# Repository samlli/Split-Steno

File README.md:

# Split Stenographic Keyboard

**current working version: rev1.1**

Open source PCB design for a mirrored keyboard with the layout below:

**rev1.x Features:**

ATmega32u4 controller  
Mirrored Alps + MX compat  
3 x 1u / 2u + 1u bottom row layout support  
THT & SMD support  
<100x100mm square PCB size  
QMK firmware

**rev2.x Features:**

ATxmega controller  
nRF24L01+ wireless  
Per-key LED backlighting  
WS2812b underglow   
Wired & coin cell battery support  
Trackpoint support  
KeyPlus firmware

**rev3.x Features:**
Minimized PCB layout
Removed mirrored compat

## Build Guide

**required parts**

Quantities are for a single PCB, double required quantities if you build two halves!

- 1x Atxmega32a4u
- 17-18x MX / Alps switches
- 0-1x PCB mount stabilizer
- 1x PJ-320A TRRS jack
- 1x Hirose 5S8 USB Mini B
- 1x Fuse
- 4x 0.1uF Capacitors
- 1x 10uF Capacitor
- 2x 4.7k Resistor
- 1x Voltage Regulator (component name needed)

## Setup

Fancy K+ stuff goes here I guess

## Why?

**why is this keyboard a thing?**

Good question - I'm not quite sure to be honest... when you find out, let me know please

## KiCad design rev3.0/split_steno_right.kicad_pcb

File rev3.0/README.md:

# rev3.0

**Features:**

Minimized PCB footprint  
Lite version with core functionality only  
NRF and RGB moved to breakouts  
Routed GND with 0 vias

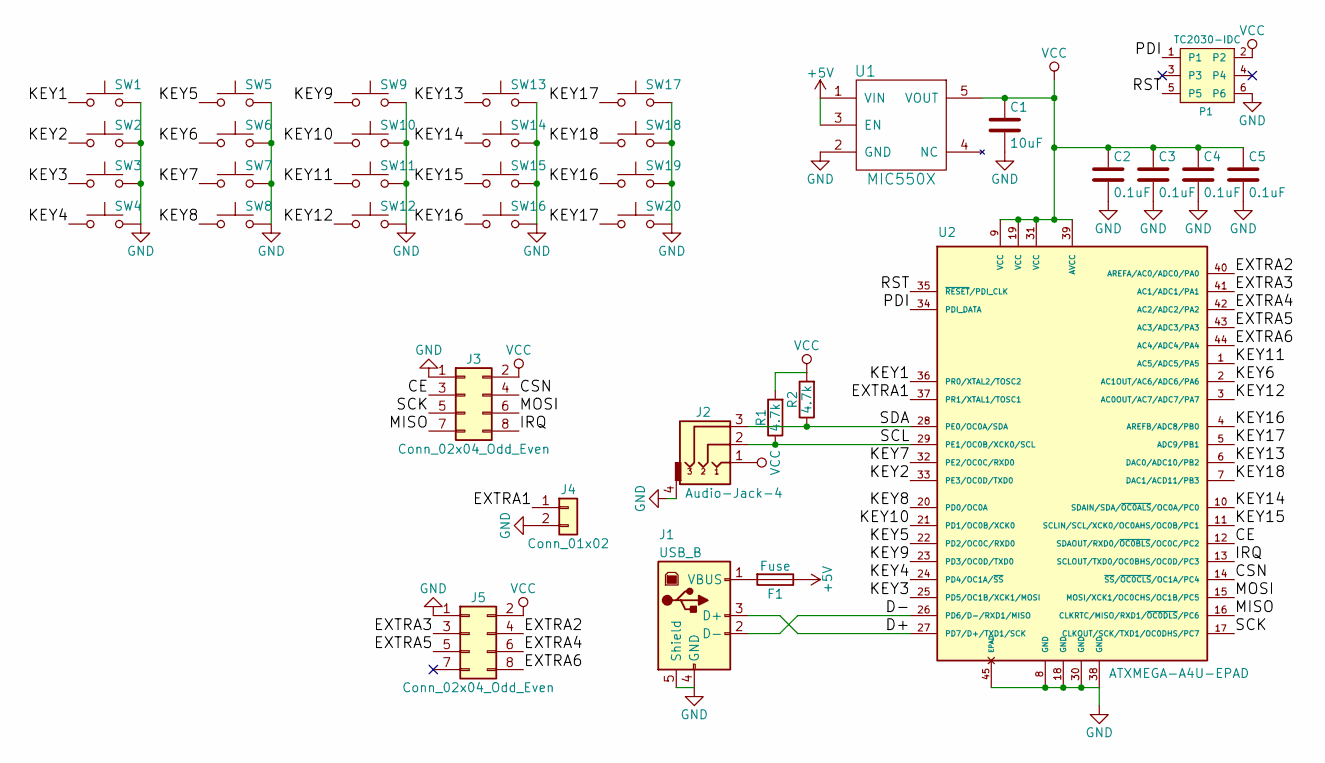
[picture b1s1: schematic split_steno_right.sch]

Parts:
C1: 10uF; C_0603_HandSoldering
C2, C3, C4, C5: 0.1uF; C_0603_HandSoldering
F1: Fuse; Fuse_SMD1206_HandSoldering
J1: USB_B; USB_miniB_hirose_5S8
J2: Audio-Jack-4; TRRS-PJ-320A
J3, J5: Conn_02x04_Odd_Even; Pin_Header_Straight_2x04_Pitch2.54mm
J4: Conn_01x02; Pin_Header_Straight_1x02_Pitch2.54mm
P1: TC2030-IDC; TC2030-NL_SMALL_AND_IDC_PDI
R1, R2: 4.7k; R_0603_HandSoldering
SW1, SW2, SW3, SW4, SW5, SW6, SW7, SW8, SW9, SW10, SW11, SW12, SW13, SW14, SW15, SW16, SW17, SW18: SW_Push; MX-1U-NoLED
SW19, SW20: SW_Push; MX-2U-NoLED
U1: MIC550X; SOT-23-5_HandSoldering
U2: ATXMEGA-A4U-EPAD; TQFP-44_10x10mm_Pitch0.8mm

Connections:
+5V: F1.1, U1.1 (VIN), U1.3 (EN)
/CE: J3.3, U2.12 (SDAOUT/RXD0/~OC0BLS~/OC0C/PC2)
/CSN: J3.4, U2.14 (~SS~/~OC0CLS~/OC1A/PC4)
/D+: J1.3 (D+), U2.27 (PD7/D+/TXD1/SCK)
/D-: J1.2 (D-), U2.26 (PD6/D-/RXD1/MISO)
/EXTRA1: J4.1, U2.37 (PR1/XTAL1/TOSC1)
/EXTRA2: J5.4, U2.40 (AREFA/AC0/ADC0/PA0)
/EXTRA3: J5.3, U2.41 (AC1/ADC1/PA1)
/EXTRA4: J5.6, U2.42 (AC2/ADC2/PA2)
/EXTRA5: J5.5, U2.43 (AC3/ADC3/PA3)
/EXTRA6: J5.8, U2.44 (AC4/ADC4/PA4)
/IRQ: J3.8, U2.13 (SCLOUT/TXD0/OC0BHS/OC0D/PC3)
/KEY1: SW1.1, U2.36 (PR0/XTAL2/TOSC2)
/KEY2: SW2.1, U2.33 (PE3/OC0D/TXD0)
/KEY3: SW3.1, U2.25 (PD5/OC1B/XCK1/MOSI)
/KEY4: SW4.1, U2.24 (PD4/OC1A/~SS~)
/KEY5: SW5.1, U2.22 (PD2/OC0C/RXD0)
/KEY6: SW6.1, U2.2 (AC1OUT/AC6/ADC6/PA6)
/KEY7: SW7.1, U2.32 (PE2/OC0C/RXD0)
/KEY8: SW8.1, U2.20 (PD0/OC0A)
/KEY9: SW9.1, U2.23 (PD3/OC0D/TXD0)
/KEY10: SW10.1, U2.21 (PD1/OC0B/XCK0)
/KEY11: SW11.1, U2.1 (AC5/ADC5/PA5)
/KEY12: SW12.1, U2.3 (AC0OUT/AC7/ADC7/PA7)
/KEY13: SW13.1, U2.6 (DAC0/ADC10/PB2)
/KEY14: SW14.1, U2.10 (SDAIN/SDA/~OC0ALS~/OC0A/PC0)
/KEY15: SW15.1, U2.11 (SCLIN/SCL/XCK0/OC0AHS/OC0B/PC1)
/KEY16: SW16.1, SW19.1, U2.4 (AREFB/ADC8/PB0)
/KEY17: SW17.1, SW20.1, U2.5 (ADC9/PB1)
/KEY18: SW18.1, U2.7 (DAC1/ACD11/PB3)
/MISO: J3.7, U2.16 (CLKRTC/MISO/RXD1/~OC0DLS~/PC6)
/MOSI: J3.6, U2.15 (MOSI/XCK1/OC0CHS/OC1B/PC5)
/PDI: P1.1, U2.34 (PDI_DATA)
/RST: P1.5, U2.35 (~RESET~/PDI_CLK)
/SCK: J3.5, U2.17 (CLKOUT/SCK/TXD1/OC0DHS/PC7)
/SCL: J2.2, R1.1, U2.29 (PE1/OC0B/XCK0/SCL)
/SDA: J2.3, R2.1, U2.28 (PE0/OC0A/SDA)
GND: C1.2, C2.2, C3.2, C4.2, C5.2, J1.4 (GND), J1.5 (Shield), J1.6, J2.4, J3.1, J4.2, J5.1, P1.6, SW1.2, SW2.2, SW3.2, SW4.2, SW5.2, SW6.2, SW7.2, SW8.2, SW9.2, SW10.2, SW11.2, SW12.2, SW13.2, SW14.2, SW15.2, SW16.2, SW17.2, SW18.2, SW19.2, SW20.2, U1.2 (GND), U2.8 (GND), U2.18 (GND), U2.30 (GND), U2.38 (GND), U2.45 (EPAD)
unnamed: F1.2, J1.1 (VBUS)
VCC: C1.1, C2.1, C3.1, C4.1, C5.1, J2.1, J3.2, J5.2, P1.2, R1.2, R2.2, U1.5 (VOUT), U2.9 (VCC), U2.19 (VCC), U2.31 (VCC), U2.39 (AVCC)

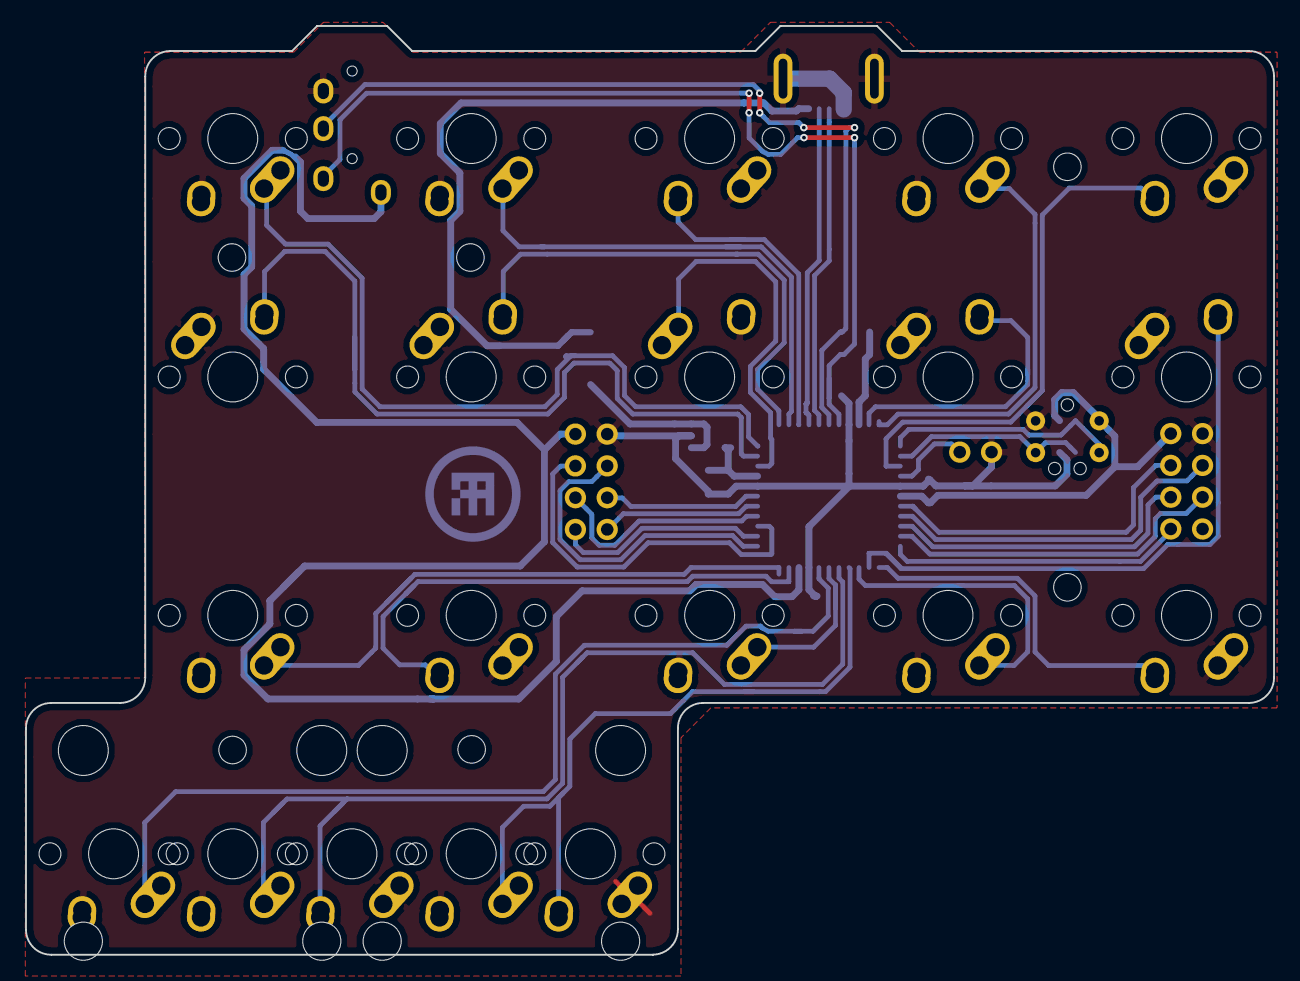
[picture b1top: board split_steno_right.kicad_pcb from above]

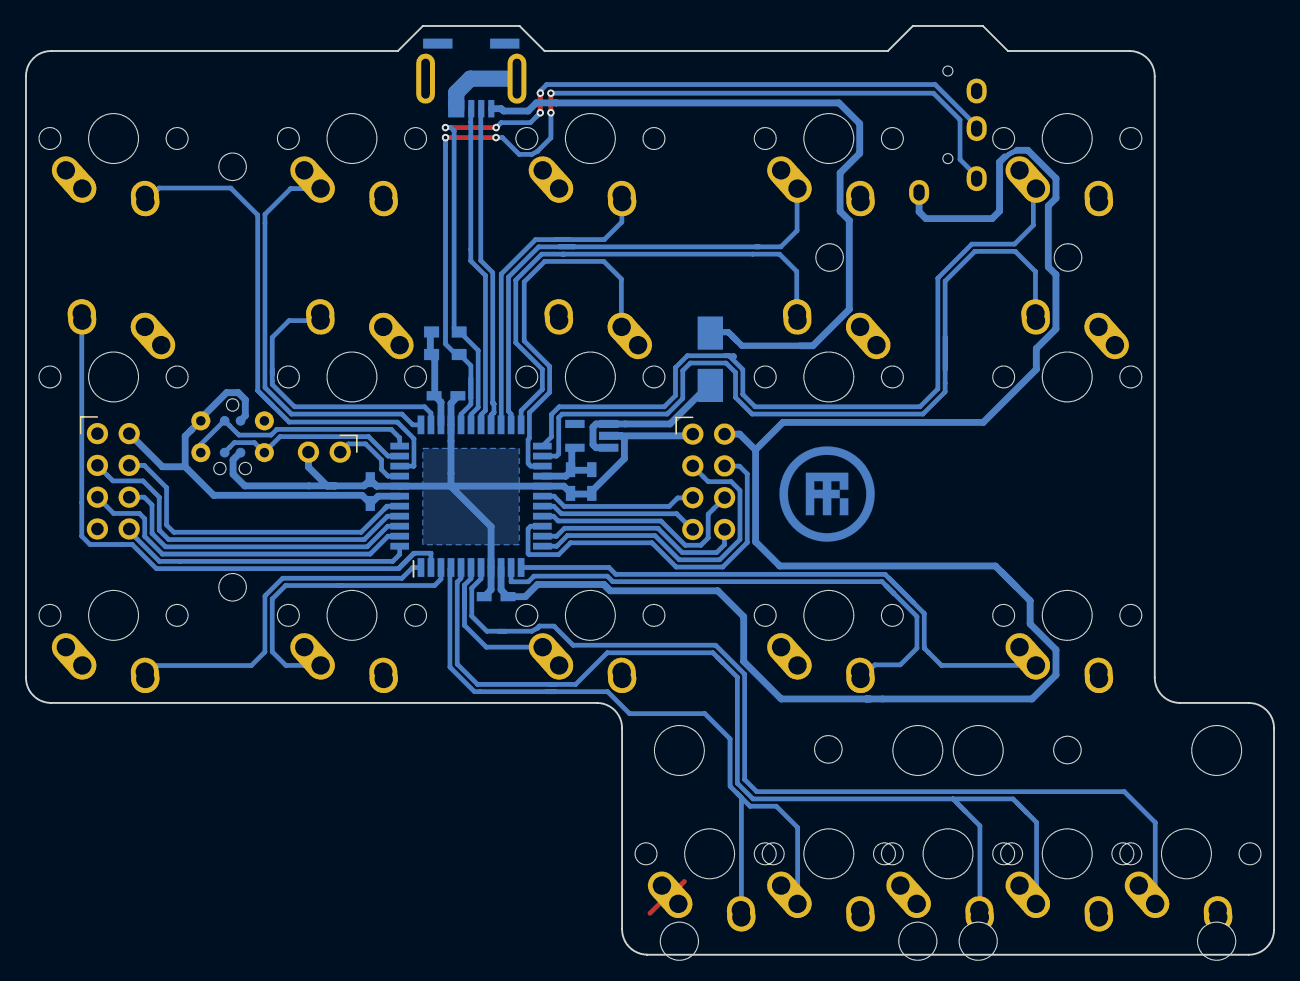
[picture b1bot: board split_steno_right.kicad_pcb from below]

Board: 2 copper layers, 99.7 x 74.2 mm, 42 parts (16 on the bottom side), 40 nets.

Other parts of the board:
M2, M2#2, M2#3, M2#4, M2#5, M2#6: MountingHole_2.2mm_M2

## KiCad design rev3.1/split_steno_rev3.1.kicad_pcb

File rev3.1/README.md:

# rev3.0

**Features:**

Integrated ATxmega controller  
SMD only  
No Diodes   
Wireless NRF

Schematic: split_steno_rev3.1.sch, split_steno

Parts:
BT1: Battery; CR2032_BK-913
C1, C2, C3, C4, C5, C6, C9, C10, C11, C12: 0.1uF; C_0603_HandSoldering
C8: 1uF; C_0603_HandSoldering
C13: 10uF; C_0603_HandSoldering
C14: 47uF; C_0603_HandSoldering
D1: D_Schottky_x2_KCom_AAK; SOT-23_Handsoldering
F1: Fuse; Fuse_SMD1206_HandSoldering
J1: USB_OTG; USB_miniB_hirose_5S8
J2: Audio-Jack-4; TRRS-PJ-320A
J3: Conn_01x03; Pin_Header_Straight_1x03_Pitch2.54mm
JP1: BAT CHK; Jumper_1x02_P2.54mm_THT
JP2: NO SW; Jumper_1x02_P2.54mm_THT
LED1, LED2, LED3, LED4, LED5, LED6: WS2812B
P1: TC2030-IDC; TC2030-NL_SMALL_AND_IDC_PDI
R4, R5: 100k; R_0603_HandSoldering
R6: 10k; R_0603_HandSoldering
R7, R8: 4.7k; R_0603_HandSoldering
SW1, SW2, SW3, SW4, SW5, SW6, SW7, SW8, SW9, SW10, SW11, SW12, SW13, SW14, SW15, SW16, SW17, SW18: SW_Push; MX-1U-NoLED
SW19, SW20: SW_Push; MX-2U-NoLED
SW21: SW_Push; SW_Tactile_SPST_Angled_MJTP1117
SW22: Switch-6P-2S2T; SlideSwitch_C&K_JS202011CQN
U1: 74LVC1G34; SOT-353_SC-70-5_Handsoldering
U4: MCP1700; SOT-23_Handsoldering
U5: ATXMEGA128A4U-AU; TQFP-44_10x10mm_Pitch0.8mm
U6: nRF24L01_module; NRF24L01-Module-SMD

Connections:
+3V3: J2.1, R7.1, R8.1
+5V: C1.1, C2.1, C3.1, C4.1, C5.1, C6.1, F1.2, LED1.1 (VDD), LED2.1 (VDD), LED3.1 (VDD), LED4.1 (VDD), LED5.1 (VDD), LED6.1 (VDD), R4.1, U1.5 (VCC), U4.3 (VI)
+BATT: D1.2, JP2.2, SW22.1, SW22.4
/BAT_LVL: JP1.2, U5.32 (PE2/OC0C/RXD0)
/CE: U5.13 (SCLOUT/TXD0/OC0BHS/OC0D/PC3), U6.3 (CE)
/CSN: U5.14 (~SS~/~OC0CLS~/OC1A/PC4), U6.4 (CSN)
/D+: J1.3 (D+), U5.27 (PD7/D+/TXD1/SCK/CLKOUT/EVOUT)
/D-: J1.2 (D-), U5.26 (PD6/D-/RXD1/MISO)
/IRQ: U5.12 (SDAOUT/RXD0/~OC0BLS~/OC0C/PC2), U6.8 (IRQ)
/KEY1: SW1.1, U5.25 (PD5/OC1B/XCK1/MOSI)
/KEY2: SW2.1, U5.24 (PD4/OC1A/~SS~)
/KEY3: SW3.1, U5.5 (ADC9/PB1)
/KEY4: SW4.1, U5.4 (AREFB/ADC8/PB0)
/KEY5: SW5.1, U5.3 (AC0OUT/AC7/ADC7/PA7)
/KEY6: SW6.1, U5.22 (PD2/OC0C/RXD0)
/KEY7: SW7.1, U5.23 (PD3/OC0D/TXD0)
/KEY8: SW8.1, U5.41 (AC1/ADC1/PA1)
/KEY9: SW9.1, U5.1 (AC5/ADC5/PA5)
/KEY10: SW10.1, U5.2 (AC1OUT/AC6/ADC6/PA6)
/KEY11: SW11.1, U5.21 (PD1/OC0B/XCK0)
/KEY12: SW12.1, U5.20 (PD0/OC0A)
/KEY13: SW13.1, U5.40 (AREFA/AC0/ADC0/PA0)
/KEY14: SW14.1, U5.37 (PR1/XTAL1/TOSC1)
/KEY15: SW15.1, U5.36 (PR0/XTAL2/TOSC2)
/KEY16: SW16.1, U5.42 (AC2/ADC2/PA2)
/KEY17: SW17.1, SW19.1, U5.43 (AC3/ADC3/PA3)
/KEY18: SW18.1, SW20.1, U5.44 (AC4/ADC4/PA4)
/MISO: U5.16 (CLKRTC/MISO/RXD1/~OC0DLS~/PC6), U6.7 (MISO)
/MOSI: U5.15 (MOSI/XCK1/OC0CHS/OC1B/PC5), U6.6 (MOSI)
/PDI: P1.1, U5.34 (PDI_DATA)
/RST: P1.5, R6.2, SW21.2, U5.35 (~RESET~/PDI_CLK)
/SCK: U5.17 (EVOUT/CLKOUT/SCK/TXD1/OC0DHS/PC7), U6.5 (SCK)
/SCL: J2.2, R8.2, U5.29 (PE1/OC0B/XCK0/SCL)
/SDA: J2.3, R7.2, U5.28 (PE0/OC0A/SDA)
/UNDER_LED: U1.2, U5.11 (SCLIN/SCL/XCK0/OC0AHS/OC0B/PC1)
/VBUS_CHECK: R4.2, R5.1, U5.33 (PE3/OC0D/TXD0)
GND: BT1.2, C1.2, C2.2, C3.2, C4.2, C5.2, C6.2, C8.2, C9.2, C10.2, C11.2, C12.2, C13.2, C14.2, J1.5 (GND), J2.4, LED1.3 (VSS), LED2.3 (VSS), LED3.3 (VSS), LED4.3 (VSS), LED5.3 (VSS), LED6.3 (VSS), P1.6, R5.2, SW1.2, SW2.2, SW3.2, SW4.2, SW5.2, SW6.2, SW7.2, SW8.2, SW9.2, SW10.2, SW11.2, SW12.2, SW13.2, SW14.2, SW15.2, SW16.2, SW17.2, SW18.2, SW19.2, SW20.2, SW21.1, U1.3 (GND), U4.1 (GND), U5.8 (GND), U5.18 (GND), U5.30 (GND), U5.38 (GND), U6.2 (VSS)
unnamed: BT1.1, JP1.1, JP2.1, SW22.2, SW22.5
unnamed: C8.1, D1.1, U4.2 (VO)
unnamed: F1.1, J1.1 (VBUS)
unnamed: J3.1, U5.6 (DAC0/ADC10/PB2)
unnamed: J3.2, U5.7 (DAC1/ACD11/PB3)
unnamed: J3.3, U5.10 (SDAIN/SDA/~OC0ALS~/OC0A/PC0)
unnamed: LED1.2 (DOUT), LED2.4 (DIN)
unnamed: LED1.4 (DIN), U1.4
unnamed: LED2.2 (DOUT), LED3.4 (DIN)
unnamed: LED3.2 (DOUT), LED4.4 (DIN)
unnamed: LED4.2 (DOUT), LED5.4 (DIN)
unnamed: LED5.2 (DOUT), LED6.4 (DIN)
VCC: C9.1, C10.1, C11.1, C12.1, C13.1, C14.1, D1.3, P1.2, R6.1, U5.9 (VCC), U5.19 (VCC), U5.31 (VCC), U5.39 (AVCC), U6.1 (VDD)

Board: 2 copper layers, 65 parts (39 on the bottom side), 50 nets, no tracks yet.

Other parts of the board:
M2, M2#2, M2#3, M2#4, M2#5, M2#6: MountingHole_2.2mm_M2

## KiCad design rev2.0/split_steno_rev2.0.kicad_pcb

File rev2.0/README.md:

# rev2.0

**WARNING: INCOMPLETE/ABANDONED**

Reason: big forehead, decided to scrap and proceed with 2.1

**Features:**

Integrated ATxmega controller  
SMD only  
No Diodes  
Reversible PCB

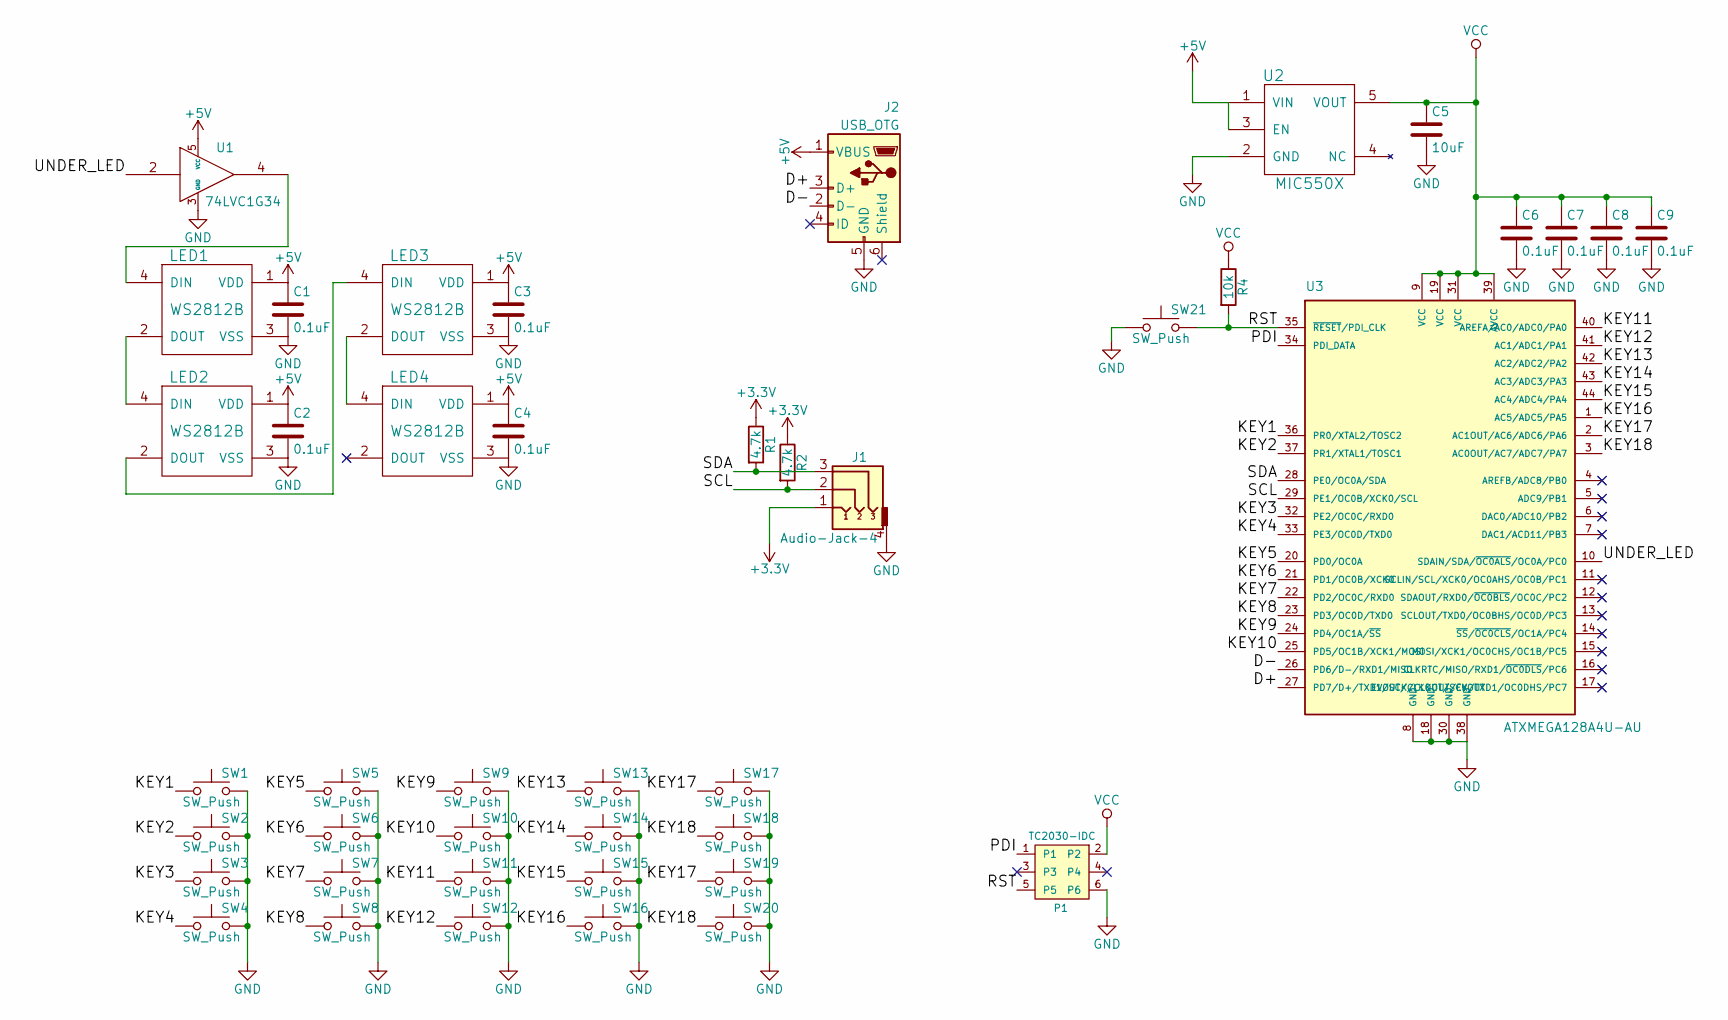
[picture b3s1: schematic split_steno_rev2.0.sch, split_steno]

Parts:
C1, C2, C3, C4, C6, C7, C8, C9: 0.1uF; C_0603_HandSoldering
C5: 10uF; C_0603_HandSoldering
J1: Audio-Jack-4; TRRS-PJ-320A
J2: USB_OTG; USB_miniB
LED1, LED2, LED3, LED4: WS2812B
P1: TC2030-IDC; Tag-Connect_TC2030-IDC-NL
R1, R2: 4.7k; R_0603_HandSoldering
R4: 10k; R_0603_HandSoldering
SW1, SW2, SW3, SW4, SW5, SW6, SW7, SW8, SW9, SW10, SW11, SW12, SW13, SW14, SW15, SW16, SW17, SW18: SW_Push; Hybrid_PCB_100H_Dual_hole
SW19, SW20: SW_Push; Hybrid_PCB_200H-dual-nosilk
SW21: SW_Push; SwitchPush_C&K_MultiFoot_RS-187R05A2-DS_And_PTS645_SMT
U1: 74LVC1G34; SOT-353_SC-70-5_Handsoldering
U2: MIC550X; SOT-23-5_HandSoldering
U3: ATXMEGA128A4U-AU; TQFP-44_10x10mm_Pitch0.8mm

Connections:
+3V3: J1.1, R1.1, R2.1
+5V: C1.1, C2.1, C3.1, C4.1, J2.1 (VBUS), LED1.1 (VDD), LED2.1 (VDD), LED3.1 (VDD), LED4.1 (VDD), U1.5 (VCC), U2.1 (VIN), U2.3 (EN)
/D+: J2.3 (D+), U3.27 (PD7/D+/TXD1/SCK/CLKOUT/EVOUT)
/D-: J2.2 (D-), U3.26 (PD6/D-/RXD1/MISO)
/KEY1: SW1.1, U3.36 (PR0/XTAL2/TOSC2)
/KEY2: SW2.1, U3.37 (PR1/XTAL1/TOSC1)
/KEY3: SW3.1, U3.32 (PE2/OC0C/RXD0)
/KEY4: SW4.1, U3.33 (PE3/OC0D/TXD0)
/KEY5: SW5.1, U3.20 (PD0/OC0A)
/KEY6: SW6.1, U3.21 (PD1/OC0B/XCK0)
/KEY7: SW7.1, U3.22 (PD2/OC0C/RXD0)
/KEY8: SW8.1, U3.23 (PD3/OC0D/TXD0)
/KEY9: SW9.1, U3.24 (PD4/OC1A/~SS~)
/KEY10: SW10.1, U3.25 (PD5/OC1B/XCK1/MOSI)
/KEY11: SW11.1, U3.40 (AREFA/AC0/ADC0/PA0)
/KEY12: SW12.1, U3.41 (AC1/ADC1/PA1)
/KEY13: SW13.1, U3.42 (AC2/ADC2/PA2)
/KEY14: SW14.1, U3.43 (AC3/ADC3/PA3)
/KEY15: SW15.1, U3.44 (AC4/ADC4/PA4)
/KEY16: SW16.1, U3.1 (AC5/ADC5/PA5)
/KEY17: SW17.1, SW19.1, U3.2 (AC1OUT/AC6/ADC6/PA6)
/KEY18: SW18.1, SW20.1, U3.3 (AC0OUT/AC7/ADC7/PA7)
/PDI: P1.1, U3.34 (PDI_DATA)
/RST: P1.5, R4.2, SW21.2, U3.35 (~RESET~/PDI_CLK)
/SCL: J1.2, R2.2, U3.29 (PE1/OC0B/XCK0/SCL)
/SDA: J1.3, R1.2, U3.28 (PE0/OC0A/SDA)
/UNDER_LED: U1.2, U3.10 (SDAIN/SDA/~OC0ALS~/OC0A/PC0)
GND: C1.2, C2.2, C3.2, C4.2, C5.2, C6.2, C7.2, C8.2, C9.2, J1.4, J2.5 (GND), LED1.3 (VSS), LED2.3 (VSS), LED3.3 (VSS), LED4.3 (VSS), P1.6, SW1.2, SW2.2, SW3.2, SW4.2, SW5.2, SW6.2, SW7.2, SW8.2, SW9.2, SW10.2, SW11.2, SW12.2, SW13.2, SW14.2, SW15.2, SW16.2, SW17.2, SW18.2, SW19.2, SW20.2, SW21.1, U1.3 (GND), U2.2 (GND), U3.8 (GND), U3.18 (GND), U3.30 (GND), U3.38 (GND)
unnamed: LED1.2 (DOUT), LED2.4 (DIN)
unnamed: LED1.4 (DIN), U1.4
unnamed: LED2.2 (DOUT), LED3.4 (DIN)
unnamed: LED3.2 (DOUT), LED4.4 (DIN)
VCC: C5.1, C6.1, C7.1, C8.1, C9.1, P1.2, R4.1, U2.5 (VOUT), U3.9 (VCC), U3.19 (VCC), U3.31 (VCC), U3.39 (AVCC)

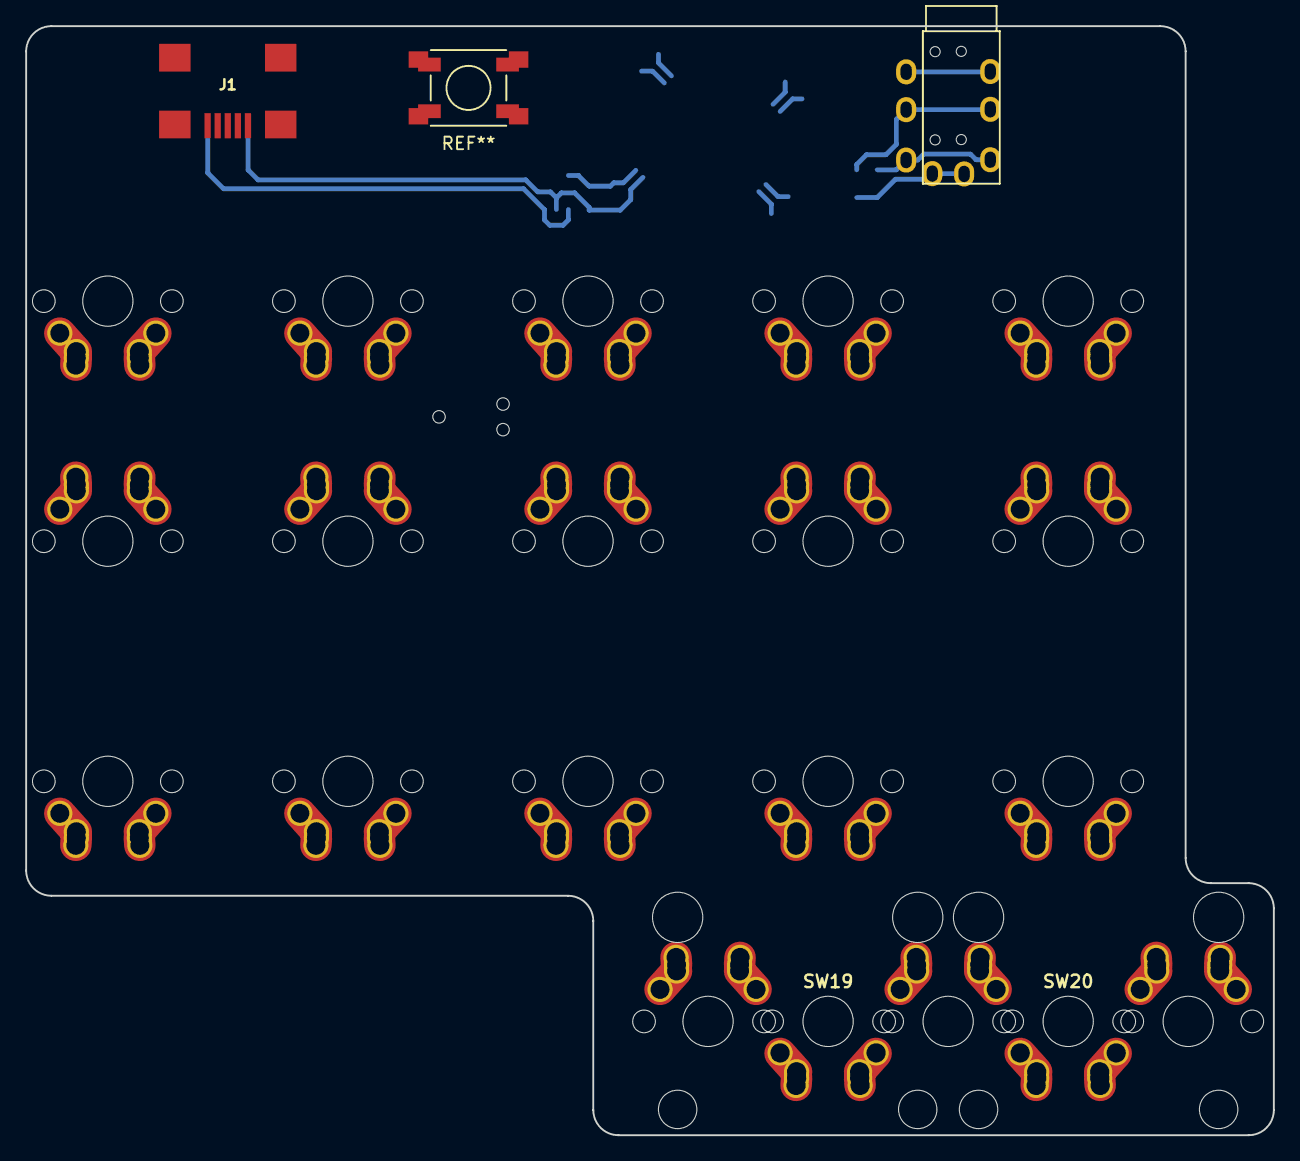
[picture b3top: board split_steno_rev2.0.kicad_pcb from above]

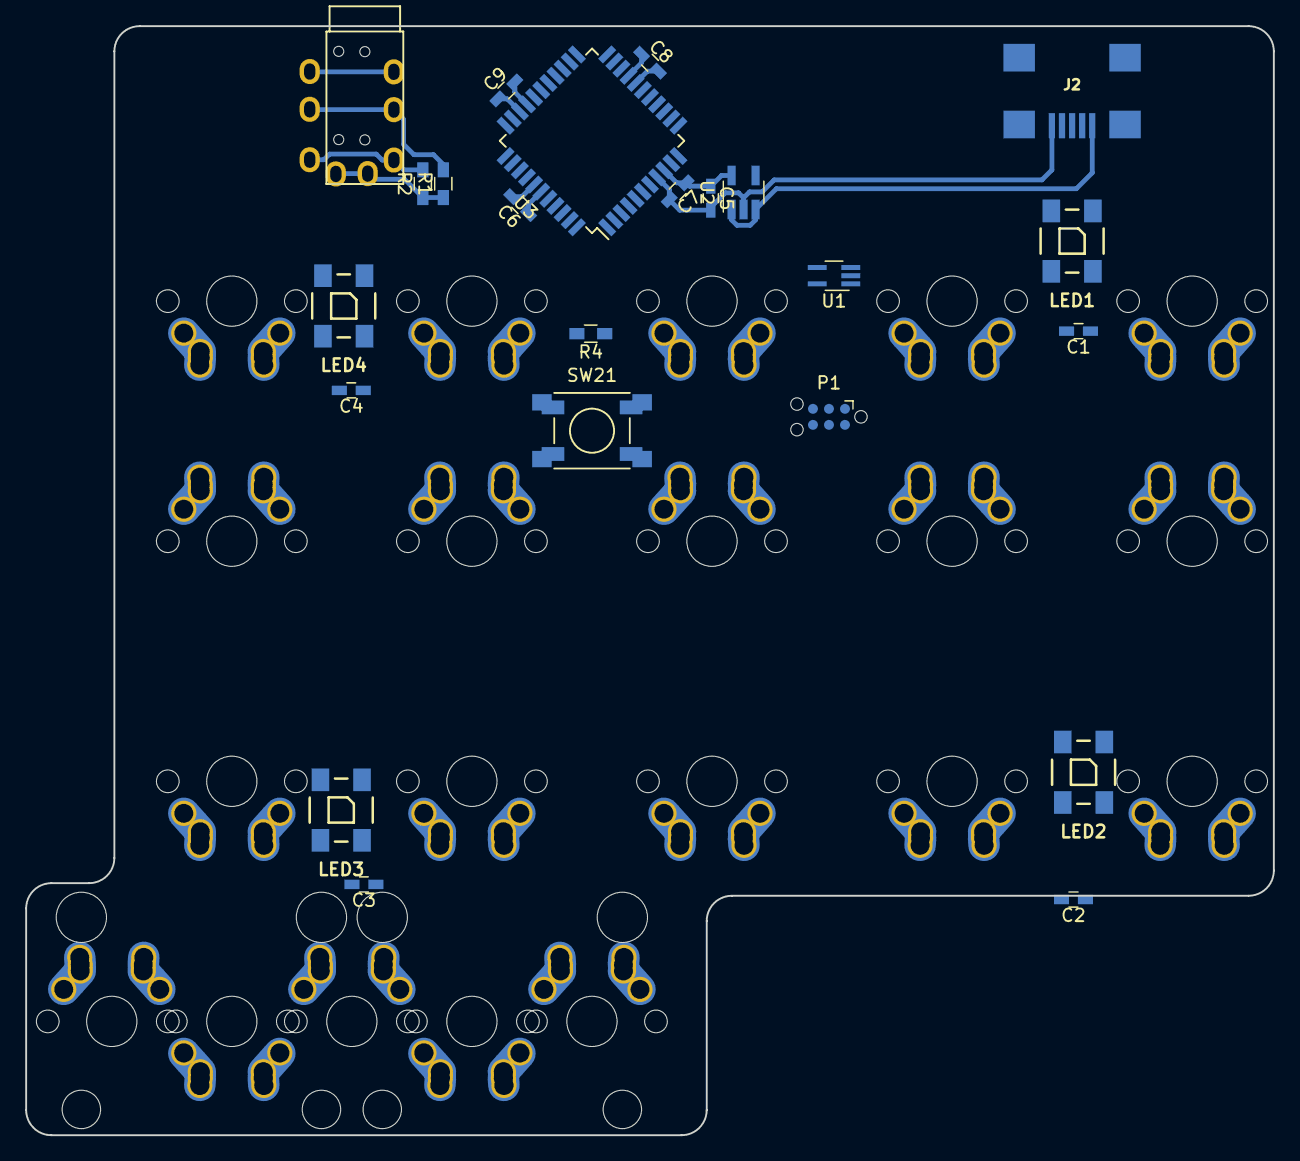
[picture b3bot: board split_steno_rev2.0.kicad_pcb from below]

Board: 2 copper layers, 99.0 x 88.0 mm, 44 parts (22 on the bottom side), 33 nets.

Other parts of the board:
J1#2: USB_B; USB_miniB

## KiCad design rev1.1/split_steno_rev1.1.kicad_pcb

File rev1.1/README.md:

# rev1.1

**left half**

**right half**

**Features:**

Pro Micro only  
Added mounting holes  
Added breakout for unused pins  
THT + SMD  
Added silkscreen design  
Cleaner routing

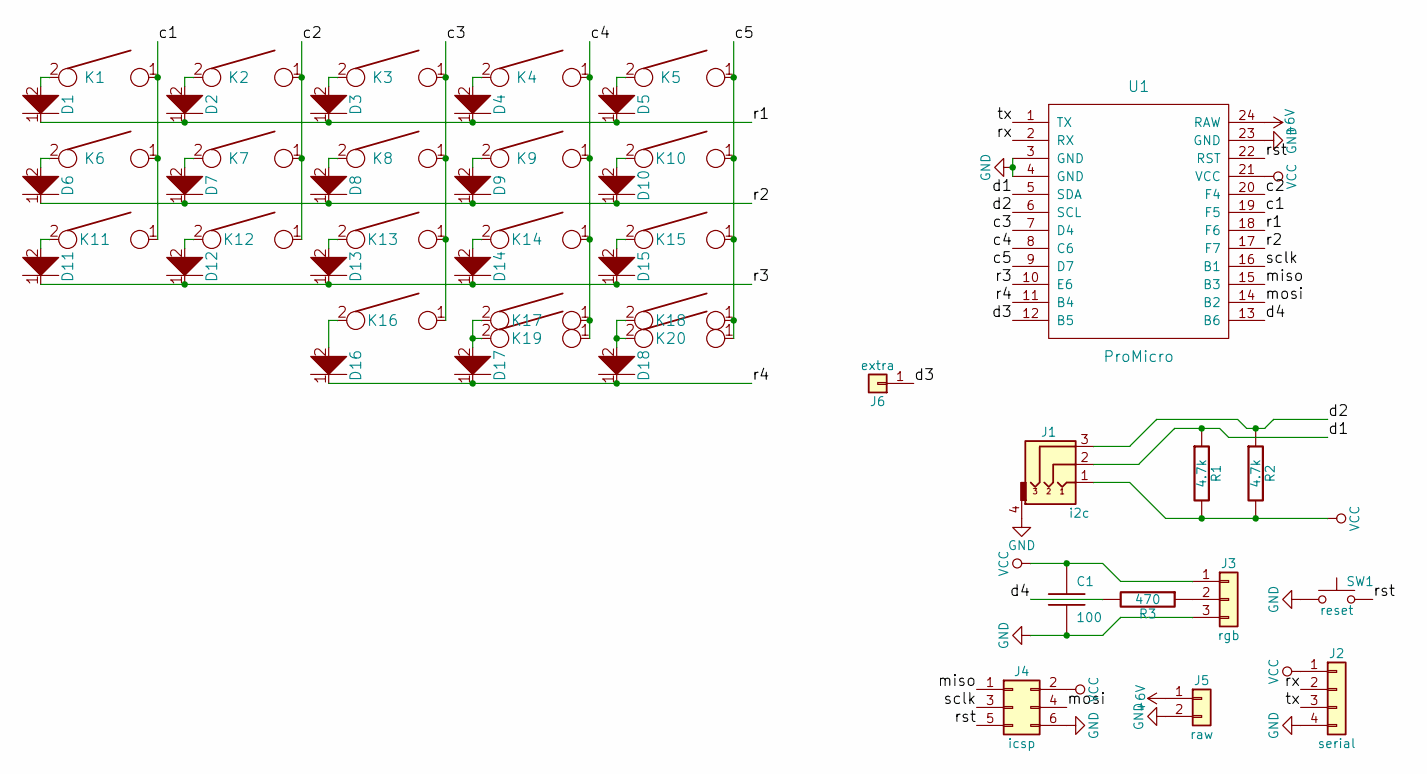
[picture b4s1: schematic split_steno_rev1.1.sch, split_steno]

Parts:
C1: 100; CP_Radial_D5.0mm_P2.00mm
D1, D2, D3, D4, D5, D6, D7, D8, D9, D10, D11, D12, D13, D14, D15, D16, D17, D18: D; Diode-dual
J1: i2c; TRRS-PJ-320A
J2: serial; Pin_Header_Straight_1x04_Pitch2.54mm
J3: rgb; Pin_Header_Straight_1x03_Pitch2.54mm
J4: icsp; Pin_Header_Straight_2x03_Pitch2.54mm
J5: raw; Pin_Header_Straight_1x02_Pitch2.54mm
J6: extra; Pin_Header_Straight_1x01_Pitch2.54mm
K1, K2, K3, K5, K6, K7, K8, K11, K12, K13, K18: KEYSW; Hybrid_PCB_100H_Dual_hole
K4, K9, K10, K14, K15, K16, K17: KEYSW; Hybrid_PCB_100H_Dual_hole-flip
K19, K20: KEYSW; Hybrid_PCB_200H-dual-nosilk
R1, R2: 4.7k; Resistor-Hybrid
R3: 470; Resistor-Hybrid
SW1: reset; SW_Tactile_SPST_Angled_MJTP1117
U1: ProMicro; ArduinoProMicro

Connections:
+6V: J5.1, U1.24 (RAW)
/c1: K1.1, K6.1, K11.1, U1.19 (F5)
/c2: K2.1, K7.1, K12.1, U1.20 (F4)
/c3: K3.1, K8.1, K13.1, K16.1, U1.7 (D4)
/c4: K4.1, K9.1, K14.1, K17.1, K19.1, U1.8 (C6)
/c5: K5.1, K10.1, K15.1, K18.1, K20.1, U1.9 (D7)
/d1: J1.2, R1.1, U1.5 (SDA)
/d2: J1.3, R2.1, U1.6 (SCL)
/d3: J6.1, U1.12 (B5)
/d4: R3.2, U1.13 (B6)
/miso: J4.1, U1.15 (B3)
/mosi: J4.4, U1.14 (B2)
/r1: D1.1, D2.1, D3.1, D4.1, D5.1, U1.18 (F6)
/r2: D6.1, D7.1, D8.1, D9.1, D10.1, U1.17 (F7)
/r3: D11.1, D12.1, D13.1, D14.1, D15.1, U1.10 (E6)
/r4: D16.1, D17.1, D18.1, U1.11 (B4)
/rst: J4.5, SW1.2, U1.22 (RST)
/rx: J2.2, U1.2 (RX)
/sclk: J4.3, U1.16 (B1)
/tx: J2.3, U1.1 (TX)
GND: C1.2, J1.4, J2.4, J3.3, J4.6, J5.2, SW1.1, U1.3 (GND), U1.4 (GND), U1.23 (GND)
unnamed: D1.2, K1.2
unnamed: D2.2, K2.2
unnamed: D3.2, K3.2
unnamed: D4.2, K4.2
unnamed: D5.2, K5.2
unnamed: D6.2, K6.2
unnamed: D7.2, K7.2
unnamed: D8.2, K8.2
unnamed: D9.2, K9.2
unnamed: D10.2, K10.2
unnamed: D11.2, K11.2
unnamed: D12.2, K12.2
unnamed: D13.2, K13.2
unnamed: D14.2, K14.2
unnamed: D15.2, K15.2
unnamed: D16.2, K16.2
unnamed: D17.2, K17.2, K19.2
unnamed: D18.2, K18.2, K20.2
unnamed: J3.2, R3.1
VCC: C1.1, J1.1, J2.1, J3.1, J4.2, R1.2, R2.2, U1.21 (VCC)

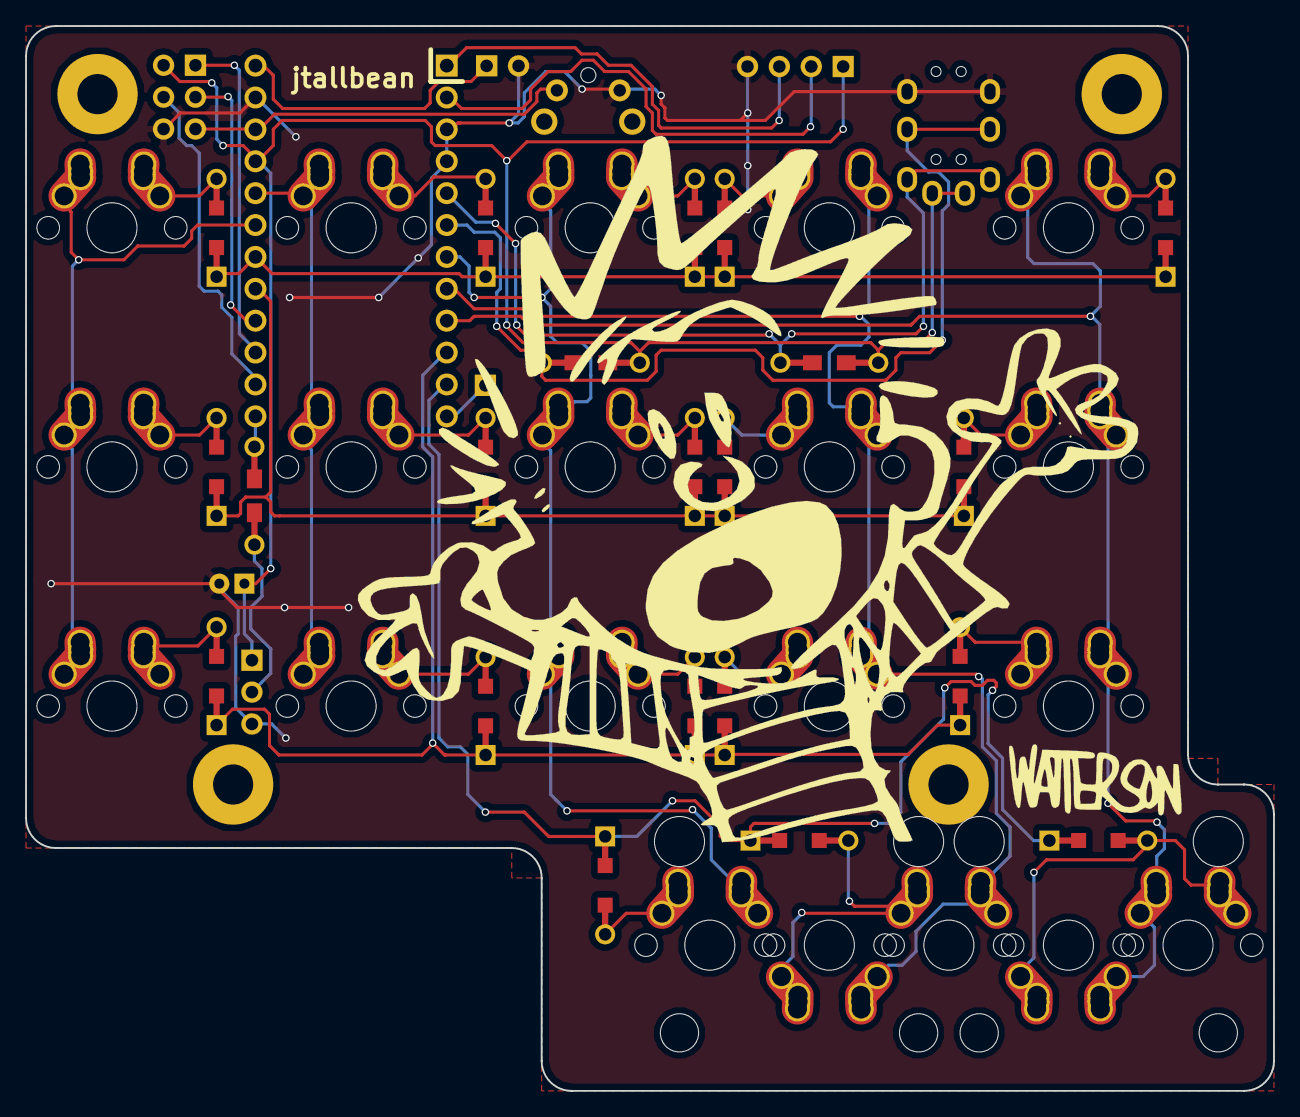
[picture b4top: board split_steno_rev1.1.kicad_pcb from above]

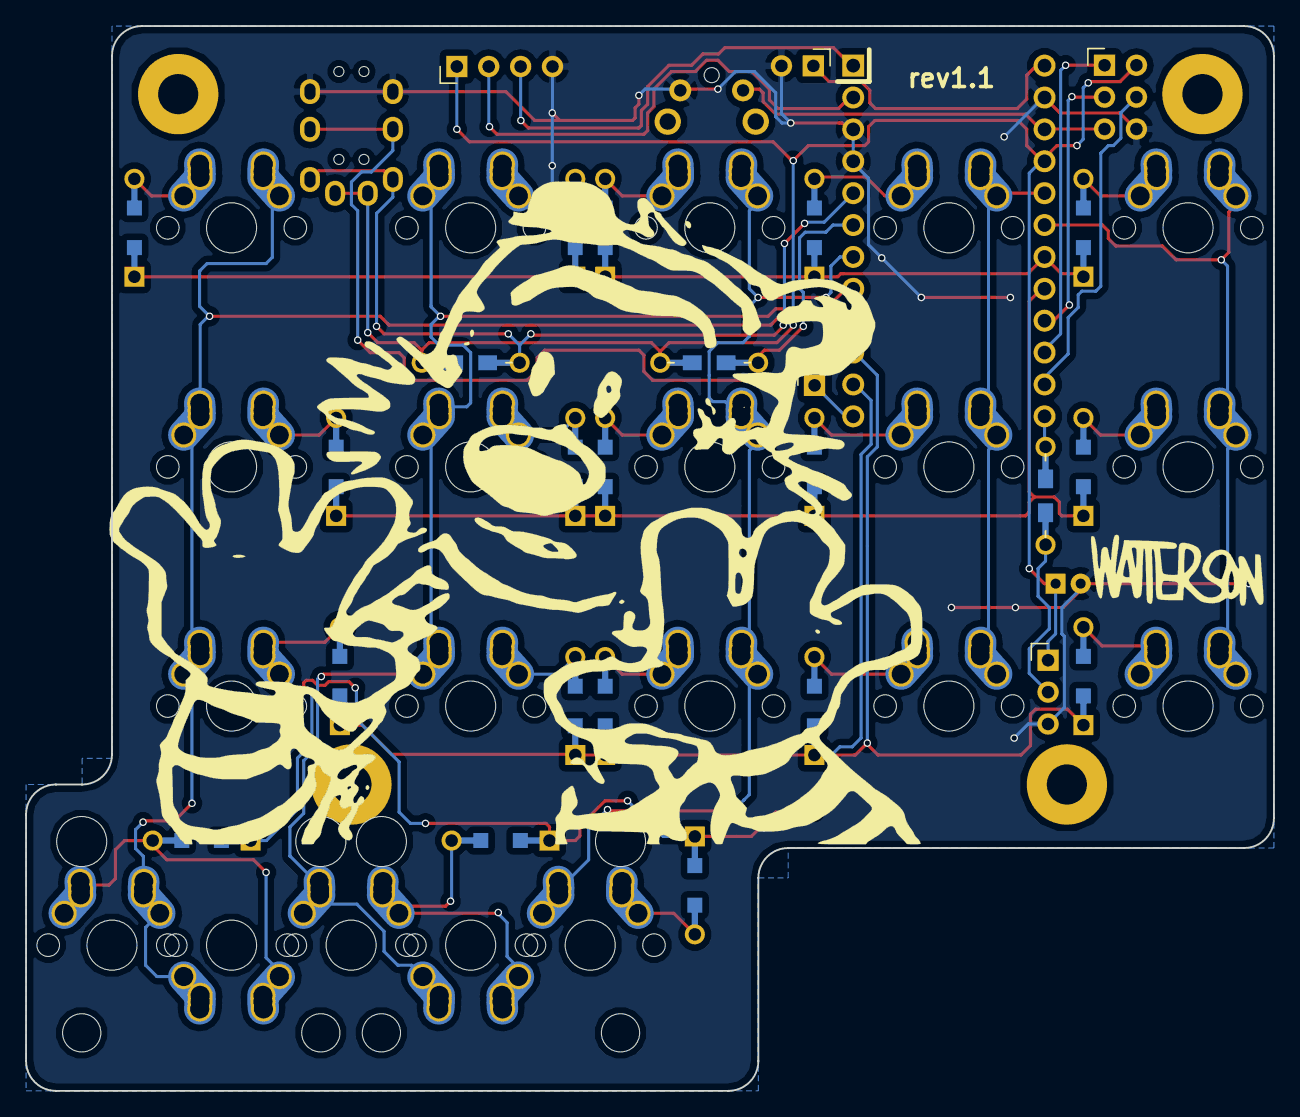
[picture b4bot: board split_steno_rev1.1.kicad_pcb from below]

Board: 2 copper layers, 99.4 x 84.8 mm, 50 parts (30 on the bottom side), 41 nets.

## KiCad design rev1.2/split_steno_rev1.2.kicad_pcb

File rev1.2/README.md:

# rev1.2

**WARNING: INCOMPLETE/ABANDONED**

**Features:**

Added LED backlighting

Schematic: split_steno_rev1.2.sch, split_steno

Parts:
C1: 100; CP_Radial_D5.0mm_P2.00mm
D1, D2, D3, D4, D5, D6, D7, D8, D9, D10, D11, D12, D13, D14, D15, D16, D17, D18: D; Diode-dual
J1: i2c; TRRS-PJ-320A
J2: serial; Pin_Header_Straight_1x04_Pitch2.54mm
J3: rgb; Pin_Header_Straight_1x03_Pitch2.54mm
J4: icsp; Pin_Header_Straight_2x03_Pitch2.54mm
J5: raw; Pin_Header_Straight_1x02_Pitch2.54mm
J6: extra; Pin_Header_Straight_1x01_Pitch2.54mm
MX1, MX2, MX3, MX4, MX5, MX6, MX7, MX8, MX9, MX10, MX11, MX12, MX13, MX14, MX15, MX16, MX18, MX20: MX-1U; Hybrid_PCB_100H_Dual_hole-LED
MX17, MX19: MX-1U; Hybrid_PCB_200H-dual-LED
Q1: BC547; TO-92_Inline_Narrow_Oval
R1, R2, R3, R4, R5, R6, R7, R8, R9, R10, R11, R12, R13, R14, R15, R16, R17, R18: 51; Resistor-Hybrid
R19: 470; Resistor-Hybrid
R20: 1k; Resistor-Hybrid
R21, R22: 4.7k; Resistor-Hybrid
SW1: reset; SW_Tactile_SPST_Angled_MJTP1117
U1: ProMicro; ArduinoProMicro

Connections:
+6V: J5.1, U1.24 (RAW)
/c1: MX1.1, MX6.1, MX11.1, U1.19 (F5)
/c2: MX2.1, MX7.1, MX12.1, U1.20 (F4)
/c3: MX3.1, MX8.1, MX13.1, MX16.1, U1.7 (D4)
/c4: MX4.2, MX9.2, MX14.2, MX17.1, MX18.2, U1.8 (C6)
/c5: MX5.1, MX10.2, MX15.2, MX19.1, MX20.1, U1.9 (D7)
/d1: J1.2, R21.1, U1.5 (SCL)
/d2: J1.3, R22.1, U1.6 (SDA)
/d3: R19.2, U1.12 (B5)
/d4: J6.1, R20.2, U1.13 (B6)
/miso: J4.1, U1.15 (B3)
/mosi: J4.4, U1.14 (B2)
/r1: D1.1, D2.1, D3.1, D4.1, D5.1, U1.18 (F6)
/r2: D6.1, D7.1, D8.1, D9.1, D10.1, U1.17 (F7)
/r3: D11.1, D12.1, D13.1, D14.1, D15.1, U1.10 (E6)
/r4: D16.1, D17.1, D18.1, U1.11 (B4)
/rst: J4.5, SW1.1, U1.22 (RST)
/rx: J2.2, U1.2 (RX)
/sclk: J4.3, U1.16 (B1)
/tx: J2.3, U1.1 (TX)
GND: C1.2, J1.4, J2.4, J3.3, J4.6, J5.2, Q1.3, SW1.2, U1.3 (GND), U1.4 (GND), U1.23 (GND)
unnamed: D1.2, MX1.2
unnamed: D2.2, MX2.2
unnamed: D3.2, MX3.2
unnamed: D4.2, MX4.1
unnamed: D5.2, MX5.2
unnamed: D6.2, MX6.2
unnamed: D7.2, MX7.2
unnamed: D8.2, MX8.2
unnamed: D9.2, MX9.1
unnamed: D10.2, MX10.1
unnamed: D11.2, MX11.2
unnamed: D12.2, MX12.2
unnamed: D13.2, MX13.2
unnamed: D14.2, MX14.1
unnamed: D15.2, MX15.1
unnamed: D16.2, MX16.2
unnamed: D17.2, MX17.2, MX18.1
unnamed: D18.2, MX19.2, MX20.2
unnamed: J3.2, R19.1
unnamed: MX1.4, R1.1
unnamed: MX2.4, R2.1
unnamed: MX3.4, R3.1
unnamed: MX4.4, R4.1
unnamed: MX5.4, R5.1
unnamed: MX6.4, R6.1
unnamed: MX7.4, R7.1
unnamed: MX8.4, R8.1
unnamed: MX9.4, R9.1
unnamed: MX10.4, R10.1
unnamed: MX11.4, R11.1
unnamed: MX12.4, R12.1
unnamed: MX13.4, R13.1
unnamed: MX14.4, R14.1
unnamed: MX15.4, R15.1
unnamed: MX16.4, R16.1
unnamed: MX17.4, MX18.4, R17.1
unnamed: MX19.4, MX20.4, R18.1
unnamed: Q1.1, R1.2, R2.2, R3.2, R4.2, R5.2, R6.2, R7.2, R8.2, R9.2, R10.2, R11.2, R12.2, R13.2, R14.2, R15.2, R16.2, R17.2, R18.2
unnamed: Q1.2, R20.1
VCC: C1.1, J1.1, J2.1, J3.1, J4.2, MX1.3, MX2.3, MX3.3, MX4.3, MX5.3, MX6.3, MX7.3, MX8.3, MX9.3, MX10.3, MX11.3, MX12.3, MX13.3, MX14.3, MX15.3, MX16.3, MX17.3, MX18.3, MX19.3, MX20.3, R21.2, R22.2, U1.21 (VCC)
